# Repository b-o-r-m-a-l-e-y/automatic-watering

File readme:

# Автополив на ATtiny13

Прошивка написана для микроконтроллера ATtiny13A. Печатная плата и схема для KiCAD находится в соответствующей папке. С кнопкой вышел косяк при разводке печатной платы, её развернуть надо и переразвести, надеюсь поправлю.

Питается от одной банки Li-ion 18650. В схеме предусмотрена микросхема  заряда аккума и контроль напряжения разряда (начнет мигать светодиод D1). В спящем режиме потребляет меньше 10 мкА и просыпается, чтобы проверить влажность почвы

## Маленькая инструкция

Клеммы датчика вставляются в земельку параллельно друг другу, насос со шлангом в воду и подключается аккумулятор. Порог сухости почвы настраивается константой `SOIL_LOW_LIMIT`, которая лежит в пределах от 0 до 255. Если напряжение на аккумуляторе опустится ниже ~3.4В, при каждой проверке светодиод будет моргать 2 раза. Пороговое напряжение задается константой `BATTERY_LOW_LIMIT`. В нормальном режиме один раз моргает светодиодом при проверке датчиков.

## По схеме

- Транзистор Q1 нужен, чтобы ток через датчик почвы протекал только в момент измерения (когда транизстор открыт)
- Q2 - включает/выключает насос
- R6/R7 - делитель для сравнения напряжения на батарее с внутренним опорным 1.1В
- R2/R3 - аналогично, но для датчика влажности почвы
- MCP73831 - микросхемка для контроля заряда аккумулятора

## По коду

Собирал компилятором avr-gcc, прошивал при помощи USBasp. Makefile присутствует. FUSE биты стандартные.

Выходит из сна (Power down) каждые 8с по прерыванию от WDG. Инкрементирует счетчик и если он больше значения  `UPDATE_TIME`, то измеряет напряжение на батарейке и на клеммах датчика. При этом моргает один раз светодиодом.

АЦП настроен в режим с левым смещением, младшие разряды опускаются, поэтому разрешение - 8 бит (от 0 до 255).

Для контроля времени включения насоса используется таймер, настроенный на счет миллисекунд. Время включения насоса регулируется константой `WATER_PUMP_TIME_MAX`.

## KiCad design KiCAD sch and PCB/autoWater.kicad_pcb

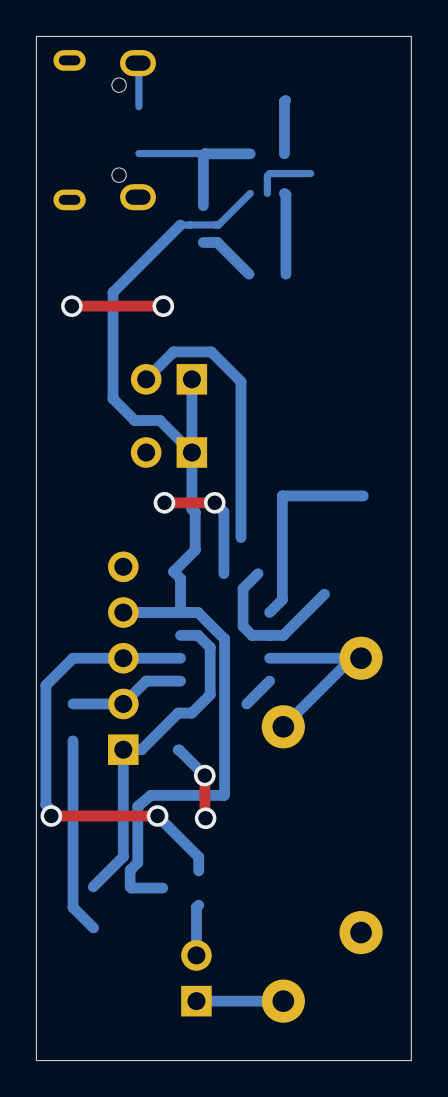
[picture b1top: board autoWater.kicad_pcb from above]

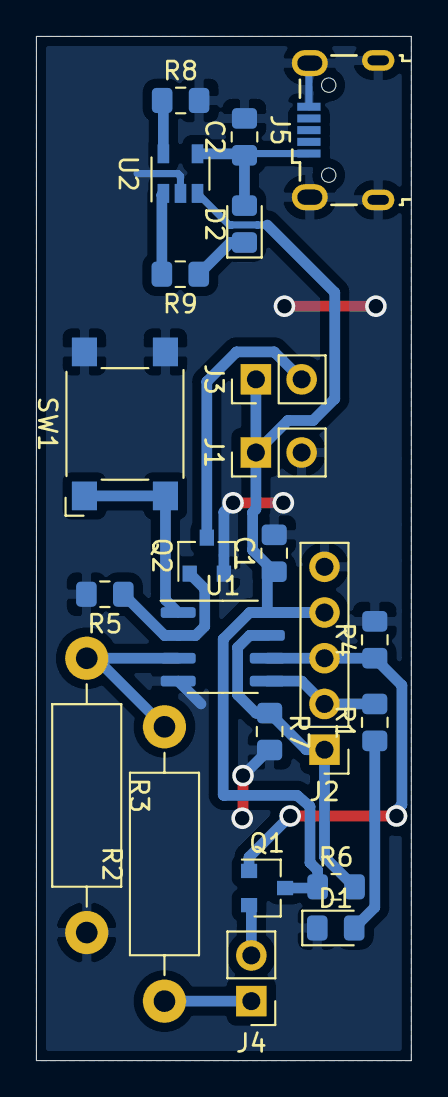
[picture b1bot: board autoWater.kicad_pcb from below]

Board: 2 copper layers, 20.8 x 56.9 mm, 23 parts (23 on the bottom side), 16 nets.

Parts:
C1: 0.1uF; C_0805_2012Metric_Pad1.15x1.40mm_HandSolder
C2: 4.7u; C_0805_2012Metric_Pad1.15x1.40mm_HandSolder
D1, D2: LED; LED_0805_2012Metric_Pad1.15x1.40mm_HandSolder
J1: Li-ion 18650; PinHeader_1x02_P2.54mm_Vertical
J2: PROG; PinHeader_1x05_P2.54mm_Vertical
J3: Water Pump; PinHeader_1x02_P2.54mm_Vertical
J4: Soil Humidity Sensor; PinHeader_1x02_P2.54mm_Vertical
J5: USB_B_Micro; USB_Micro-B_Wuerth_629105150521
Q1, Q2: AO3400; SOT-23
R1, R9: 470; R_0805_2012Metric_Pad1.15x1.40mm_HandSolder
R2: 6.8k; R_Axial_DIN0411_L9.9mm_D3.6mm_P15.24mm_Horizontal
R3: 1.5k; R_Axial_DIN0411_L9.9mm_D3.6mm_P15.24mm_Horizontal
R4, R5: 10k; R_0805_2012Metric_Pad1.15x1.40mm_HandSolder
R6: 680k; R_0805_2012Metric_Pad1.15x1.40mm_HandSolder
R7: 150k; R_0805_2012Metric_Pad1.15x1.40mm_HandSolder
R8: 2k; R_0805_2012Metric_Pad1.15x1.40mm_HandSolder
SW1: SW_Push_Dual; SW_SPST_Omron_B3FS-100xP
U1: ATtiny13-20SSU; SOIC-8_3.9x4.9mm_P1.27mm
U2: MCP73831-2-OT; SOT-23-5

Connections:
+5V: C1.1, J1.1, J2.4, J3.1, Q1.3, R6.1, U1.8, U2.3
Button: SW1.1, SW1.3, U1.1
GND: C1.2, C2.2, D1.1, J1.2, J2.5, J5.5, J5.6, Q2.2, R3.2, R4.2, R5.2, R7.2, R8.2, SW1.2, SW1.4, U1.4, U2.2
unnamed: C2.1, D2.2, J5.1, U2.4
unnamed: D1.2, R1.1
unnamed: D2.1, R9.1
unnamed: J2.1, R6.2, R7.1, U1.7
unnamed: J2.2, R1.2, U1.5
unnamed: J2.3, Q1.1, R4.1, U1.6
unnamed: J3.2, Q2.3
unnamed: Q2.1, R5.1, U1.2
unnamed: R2.2, R3.1, U1.3
unnamed: R8.1, U2.5
unnamed: R9.2, U2.1
Sensor: J4.1, R2.1
Sensor_Voltage: J4.2, Q1.2

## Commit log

2020-05-14 some shematic changes
2020-05-21 some sch changes
2020-05-23 add makefile
2020-05-26 some commit
2020-06-02 new pcb
2020-06-03 added mi ion charger on pcb
2020-06-03 added li ion charger on pcb
2020-06-03 same
2020-06-03 add pdf sch
2020-06-03 config code
2020-06-03 code
2020-06-03 resistor value change
2020-06-07 add timer service
2020-06-08 add WDG
2020-06-09 text on sch
2020-06-10 refactor code & time to test
2020-06-11 a lot of debug
2020-06-11 looks like works
2020-06-11 update levels for li-ion
2020-06-12 add readme & small code changes
2020-06-12 Rename readme to readme.md
2020-06-17 some fixes, time & blink
